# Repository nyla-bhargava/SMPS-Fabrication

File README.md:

⚡ SMPS Fabrication Project

Overview
This project involved the complete design and fabrication of a Switched-Mode Power Supply (SMPS), which efficiently converts electrical power using switching regulators. The goal was to build a compact, efficient, and low-heat-dissipating power supply prototype suitable for embedded systems and consumer electronics.

🔧 Tools & Technologies Used
    KiCad – Circuit design and PCB layout

    Soldering Iron – For manual component soldering

    Multimeter & Oscilloscope – For testing and debugging

    Etching Kit / PCB Fabrication Service – To manufacture the PCB

    Standard SMPS Components – Inductors, capacitors, MOSFETs, transformer, opto-isolators, etc.

🧩 Project Workflow
1. Circuit Design (KiCad)
2. PCB Layout & Routing
3. PCB Fabrication
4. Component Soldering
5. Testing & Debugging

(PS. The transformor arrived late)

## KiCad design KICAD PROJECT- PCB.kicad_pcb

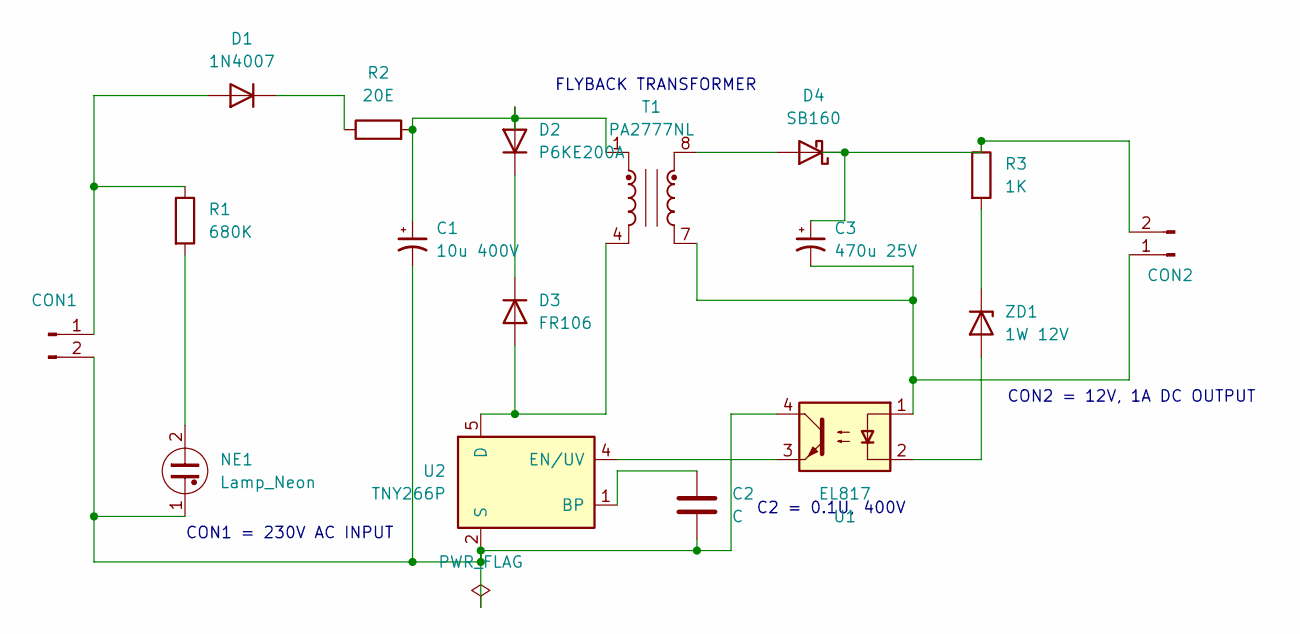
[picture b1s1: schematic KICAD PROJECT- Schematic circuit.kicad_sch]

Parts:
C1: 10u 400V; CAPPRD500W60D1250H2700
C2: C; CAPRR1500W80L1800T500H1050
C3: 470u 25V; CAPPRD500W60D1000H1700
CON1, CON2: conn_2 DC vert
D1: 1N4007; D_DO-41_SOD81_P10.16mm_Horizontal
D2: P6KE200A; DIOAD1936W88L640D324
D3: FR106; DIOAD1405W90L465D235
D4: SB160; D_DO-41_SOD81_P10.16mm_Horizontal
NE1: Lamp_Neon; LAMP_D2A
R1: 680K; 0.5w resistor 20ohm
R2: 20E; 0.5w resistor 20ohm
R3: 1K; 0.5w resistor 20ohm
T1: PA2777NL; EE20
U1: EL817; DIP-4_W7.62mm
U2: TNY266P; PowerIntegrations_PDIP-8B
ZD1: 1W 12V; DIOAD1036W78L463D272

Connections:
unnamed: CON1.1, D1.2 (A), R1.1
unnamed: C1.2, C2.2, CON1.2, NE1.1, U1.4, U2.2 (S), U2.3 (S), U2.7 (S), U2.8 (S)
unnamed: C3.2, CON2.1, T1.7, U1.1
unnamed: C3.1, CON2.2, D4.1 (K), R3.1
unnamed: D1.1 (K), R2.1
unnamed: C1.1, D2.2 (A), R2.2, T1.1
unnamed: D2.1 (K), D3.1 (K)
unnamed: D3.2 (A), T1.4, U2.5 (D)
unnamed: D4.2 (A), T1.8
unnamed: NE1.2, R1.2
unnamed: C2.1, U2.1 (BP)
unnamed: U1.3, U2.4 (EN/UV)
unnamed: U1.2, ZD1.2 (A)
unnamed: R3.2, ZD1.1 (K)

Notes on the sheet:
CON2 = 12V, 1A DC OUTPUT
CON1 = 230V AC INPUT
FLYBACK TRANSFORMER
C2 = 0.1U, 400V

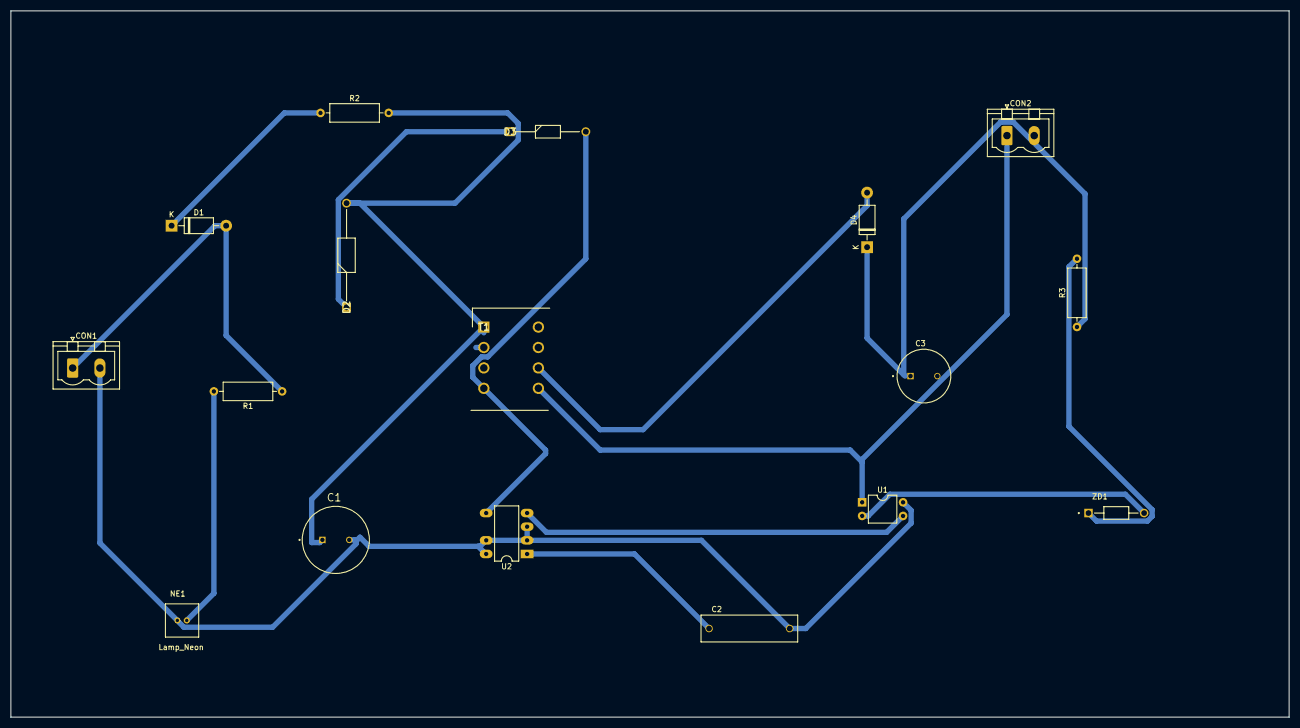
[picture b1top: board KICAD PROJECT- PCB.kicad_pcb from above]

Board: 2 copper layers, 238.0 x 131.5 mm, 17 parts (0 on the bottom side), 14 nets.
